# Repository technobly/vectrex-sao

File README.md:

# Vectrex SAO

Hardware and software files for the mini playable Vectrex SAO by Brett Walach.  Made for Hackaday Supercon 2022!

# Features
- Mini playable low res version of Scramble
- 7 x 10 White LED Charlieplexed display (placed in a slight perspective to match the Vectrex artwork!)
- Joystick is a 1-button capacitive touch controller
- PIC16F886 8K MCU (I had a reel of these I pulled out of the trash, which is why it uses this relatively old and huge MCU.)
- Speaker (auto mutes if not playing, or can permanently disable with removing a solder blob)
- Coily cord!  This is made of a solid core silicone wire, and stranded core silicone wire.  These were an absolute pain to make.
- Jumpers for hacking, control it via I2C directly if you want from a main badge... and there's PWM input for the speaker and touch controller output for sensing button presses available to wire to the SAO connector.
- What's a Vectrex? [https://wikipedia.org/wiki/Vectrex](https://wikipedia.org/wiki/Vectrex)
- **High score permanently saved!** Tweet a pic of your score @Technobly #vectrex-sao #supercon #badgelife

# BOM

- PCBs: 1.0mm, HASL finish, white silkscreen, black soldermask, gives a nice thin feel to them. NOTE: 1.0mm is thinner than standard PCBs!
- Don't forget to order both PCBs: 1) the main [console body](gerbers/vectrex-sao-v1.1.zip) and 2) the [controller](gerbers/vectrex-sao-controller-v1.1.zip)
- [bom/vectrex-sao-bom-both-sides.csv](bom/vectrex-sao-bom-both-sides.csv) contains all parts required to build the SAO, ready to upload to JLCPCB
- [bom/vectrex-sao-pos-both-sides.csv](bom/vectrex-sao-pos-both-sides.csv) contains the position of all parts required, ready to upload to JLCPCB
- Inner coily cord wire - 18 AWG solid core, black PVC jacket, outer diameter 1.6mm, 2.0" long with 0.25" stripped on both ends for a 1.5" long jacket. [Digikey 10982-18-1-2000-001-1-TD](https://www.digikey.com/en/products/detail/cnc-tech/10982-18-1-2000-001-1-TD/12749485)
- Outer coily cord wire - 26 AWG stranded core, black silicone jacket, outer diameter 1.3mm, ~27 turns, ~9" long. [Digikey 1175-3132-26-1-0500-001-1-TS-DS-ND](https://www.digikey.com/en/products/detail/cnc-tech/3132-26-1-0500-001-1-TS/15853654)

# Coily Cord Construction

#### 1. Wrap the 26 AWG stranded silicone wire around the 0.25" stripped end of the 18 AWG solid wire, but do not solder it yet.

#### 2. Add the controller PCB observing the proper orientation.

#### 3. Add a good amount of solder here, and push the board up against the wire bundle if possible (I did not push it up in this picture like I should have).

#### 4. Flush cut the excess wire, but leave a bit sticking out so has a little mechanical strength.

#### 5. Wrap the silicone wire 21-27 times (21 if diameter is 1.5mm, 27 if 1.3mm).  Wrap the wire tightly and keep pushing it down on the solid core as you go.  Finally twist the stranded wires around the end and while holding that tightly, clamp the wire bundle to prevent it from unwinding.

#### 6. Now add the main PCB obsererving the correct orientation.

#### 7. Add a good amount of solder here as well. Flush cut the excess wire, but leave a bit sticking out so has a little mechanical strength.

#### 8. The one on the left used 1.5mm 26 AWG wire so it has 21 wraps, and the one on the right has a slightly smaller diameter wire 1.3mm so it requires 27 wraps.  Both will work fine, but 27 wraps looks a little closer to reality :smile:

# Video of it in action:

[Youtube.com/PlayVectrex](https://youtu.be/AfYQyKARwps?si=DoC_TBigiWhMu1rB)

# License

Creative Commons Attribution-ShareAlike 4.0 International (CC BY-SA 4.0) - essentially do whatever you want, and if this is helpful to you [consider buying me a coffee](https://buymeacoffee.com/walach)  Full [LICENSE here](LICENSE)

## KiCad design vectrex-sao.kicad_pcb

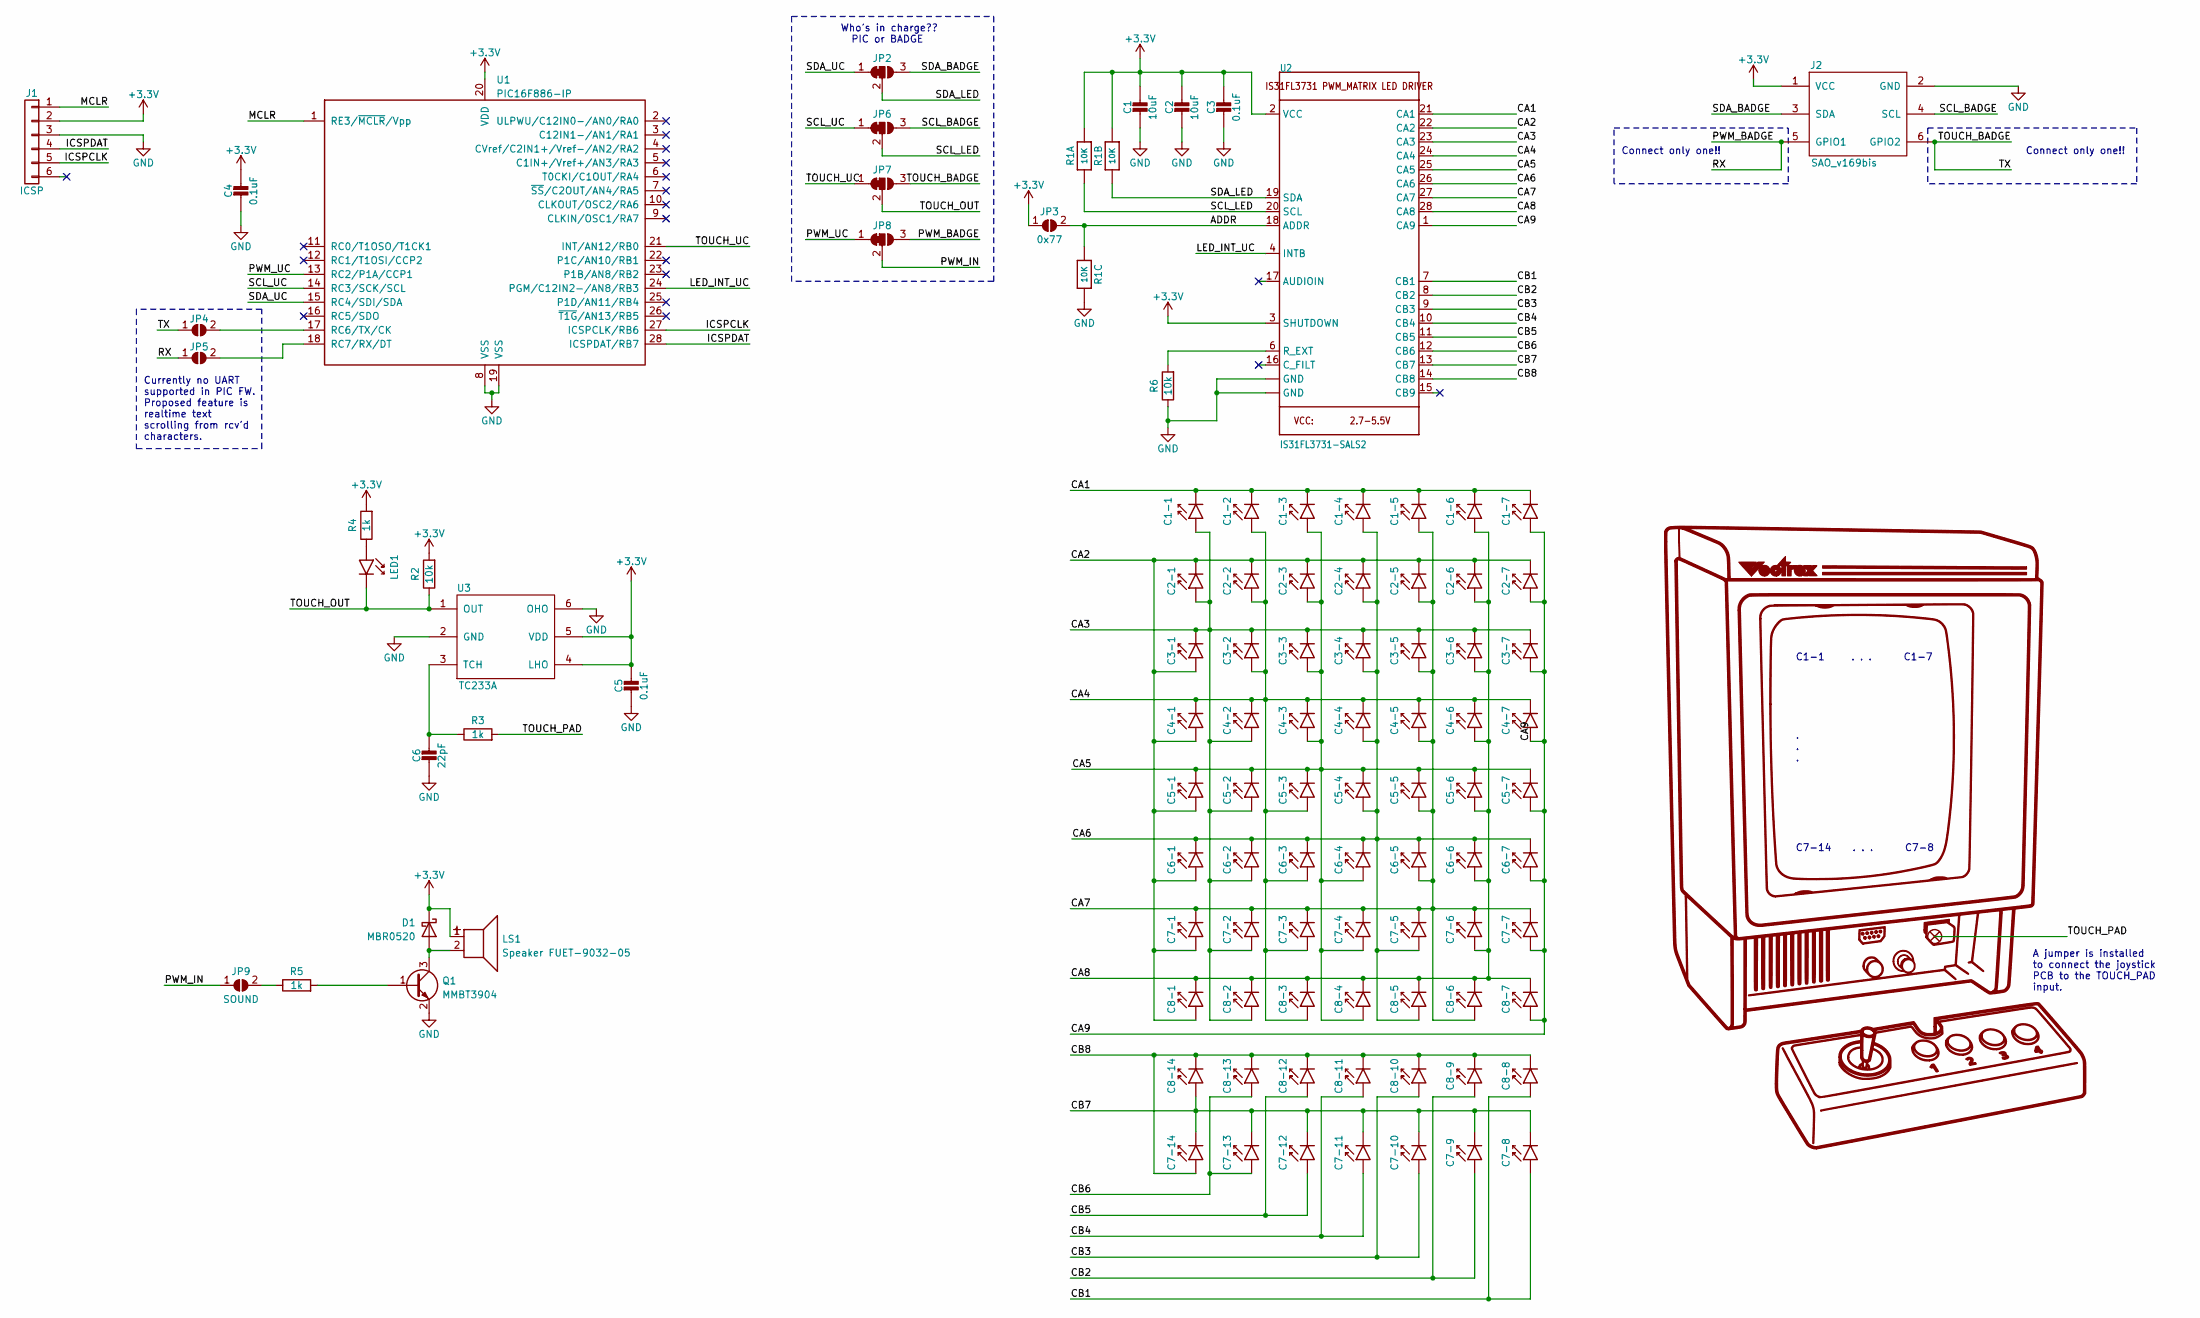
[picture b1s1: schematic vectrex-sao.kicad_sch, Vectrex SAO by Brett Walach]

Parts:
C1, C2: 10uF; C_0805_2012Metric
C1-1, C1-2, C1-3, C1-4, C1-5, C1-6, C1-7, C2-1, C2-2, C2-3, C2-4, C2-5, C2-6, C2-7, C3-1, C3-2, C3-3, C3-4, C3-5, C3-6, C3-7, C4-1, C4-2, C4-3, C4-4, C4-5, C4-6, C4-7, C5-1, C5-2, C5-3, C5-4, C5-5, C5-6, C5-7, C6-1, C6-2, C6-3, C6-4, C6-5, C6-6, C6-7, C7-1, C7-2, C7-3, C7-4, C7-5, C7-6, C7-7, C7-8, C7-9, C7-10, C7-11, C7-12, C7-13, C7-14, C8-1, C8-2, C8-3, C8-4, C8-5, C8-6, C8-7, C8-8, C8-9, C8-10, C8-11, C8-12, C8-13, C8-14: LED0603_NOOUTLINE; LED_0603_1608Metric
C3, C4: 0.1uF; C_0805_2012Metric
C5: 0.1uF; C_0603_1608Metric
C6: 22pF; C_0603_1608Metric
D1: MBR0520; D_SOD-123
J1: ICSP; PinHeader_1x06_P2.54mm_Vertical_SMD_Pin1Right
J2: SAO_v169bis; Badgelife-SAOv169-SAO-2x3
JP1: TOUCH_PAD; MountingHole_1.5mm_M2_Pad_TopOnly
JP2, JP6, JP7, JP8: solderjumper-3way; SolderJumper-3_P1.3mm_Bridged12_RoundedPad1.0x1.5mm_NumberL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
JP3: 0x77; SolderJumper-2_P1.3mm_Open_RoundedPad1.0x1.5mm
JP4: TX; SolderJumper-2_P1.3mm_Open_RoundedPad1.0x1.5mm
JP5: RX; SolderJumper-2_P1.3mm_Open_RoundedPad1.0x1.5mm
JP9: SOUND; SolderJumper-2_P1.3mm_Bridged_RoundedPad1.0x1.5mm
LED1: LED0603_NOOUTLINE; LED_0603_1608Metric
LS1: Speaker FUET-9032-05; MagneticBuzzer_FUET-9032-05
Q1: MMBT3904; SOT-23
R1: 10K; R_Array_Convex_4x0603_CAT16-F4
R2, R6: 10k; R_0603_1608Metric
R3, R4, R5: 1k; R_0603_1608Metric
U1: PIC16F886-IP; SOIC-28W_7.5x17.9mm_P1.27mm
U2: IS31FL3731-SALS2; QFN-28-1EP_4x4mm_P0.4mm_EP2.3x2.3mm
U3: TC233A; SOT-23-6

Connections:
+3.3V: C1.1, C2.1, C3.1, C4.1, C5.1, D1.1 (K), J1.2, J2.1 (VCC), JP3.1 (A), LS1.1, R1.7 (2), R1.8 (2), R2.2, R4.2, U1.20 (VDD), U2.2 (VCC), U2.3 (SHUTDOWN), U3.4 (LHO), U3.5 (VDD)
/ADDR: JP3.2 (B), R1.3 (1), U2.18 (ADDR)
/CA1: C1-1.1 (K), C1-2.1 (K), C1-3.1 (K), C1-4.1 (K), C1-5.1 (K), C1-6.1 (K), C1-7.1 (K), U2.21 (CA1)
/CA2: C2-1.1 (K), C2-2.1 (K), C2-3.1 (K), C2-4.1 (K), C2-5.1 (K), C2-6.1 (K), C2-7.1 (K), C3-1.2 (A), C4-1.2 (A), C5-1.2 (A), C6-1.2 (A), C7-1.2 (A), C8-1.2 (A), U2.22 (CA2)
/CA3: C1-1.2 (A), C2-1.2 (A), C3-1.1 (K), C3-2.1 (K), C3-3.1 (K), C3-4.1 (K), C3-5.1 (K), C3-6.1 (K), C3-7.1 (K), C4-2.2 (A), C5-2.2 (A), C6-2.2 (A), C7-2.2 (A), C8-2.2 (A), U2.23 (CA3)
/CA4: C1-2.2 (A), C2-2.2 (A), C3-2.2 (A), C4-1.1 (K), C4-2.1 (K), C4-3.1 (K), C4-4.1 (K), C4-5.1 (K), C4-6.1 (K), C4-7.1 (K), C5-3.2 (A), C6-3.2 (A), C7-3.2 (A), C8-3.2 (A), U2.24 (CA4)
/CA5: C1-3.2 (A), C2-3.2 (A), C3-3.2 (A), C4-3.2 (A), C5-1.1 (K), C5-2.1 (K), C5-3.1 (K), C5-4.1 (K), C5-5.1 (K), C5-6.1 (K), C5-7.1 (K), C6-4.2 (A), C7-4.2 (A), C8-4.2 (A), U2.25 (CA5)
/CA6: C1-4.2 (A), C2-4.2 (A), C3-4.2 (A), C4-4.2 (A), C5-4.2 (A), C6-1.1 (K), C6-2.1 (K), C6-3.1 (K), C6-4.1 (K), C6-5.1 (K), C6-6.1 (K), C6-7.1 (K), C7-5.2 (A), C8-5.2 (A), U2.26 (CA6)
/CA7: C1-5.2 (A), C2-5.2 (A), C3-5.2 (A), C4-5.2 (A), C5-5.2 (A), C6-5.2 (A), C7-1.1 (K), C7-2.1 (K), C7-3.1 (K), C7-4.1 (K), C7-5.1 (K), C7-6.1 (K), C7-7.1 (K), C8-6.2 (A), U2.27 (CA7)
/CA8: C1-6.2 (A), C2-6.2 (A), C3-6.2 (A), C4-6.2 (A), C5-6.2 (A), C6-6.2 (A), C7-6.2 (A), C8-1.1 (K), C8-2.1 (K), C8-3.1 (K), C8-4.1 (K), C8-5.1 (K), C8-6.1 (K), C8-7.1 (K), U2.28 (CA8)
/CA9: C1-7.2 (A), C2-7.2 (A), C3-7.2 (A), C4-7.2 (A), C5-7.2 (A), C6-7.2 (A), C7-7.2 (A), C8-7.2 (A), U2.1 (CA9)
/CB1: C7-8.2 (A), C8-8.2 (A), U2.7 (CB1)
/CB2: C7-9.2 (A), C8-9.2 (A), U2.8 (CB2)
/CB3: C7-10.2 (A), C8-10.2 (A), U2.9 (CB3)
/CB4: C7-11.2 (A), C8-11.2 (A), U2.10 (CB4)
/CB5: C7-12.2 (A), C8-12.2 (A), U2.11 (CB5)
/CB6: C7-13.2 (A), C8-13.2 (A), U2.12 (CB6)
/CB7: C7-8.1 (K), C7-9.1 (K), C7-10.1 (K), C7-11.1 (K), C7-12.1 (K), C7-13.1 (K), C7-14.1 (K), C8-14.2 (A), U2.13 (CB7)
/CB8: C7-14.2 (A), C8-8.1 (K), C8-9.1 (K), C8-10.1 (K), C8-11.1 (K), C8-12.1 (K), C8-13.1 (K), C8-14.1 (K), U2.14 (CB8)
/ICSPCLK: J1.5, U1.27 (ICSPCLK/RB6)
/ICSPDAT: J1.4, U1.28 (ICSPDAT/RB7)
/LED_INT_UC: U1.24 (PGM/C12IN2-/AN8/RB3), U2.4 (INTB)
/MCLR: J1.1, U1.1 (RE3/~MCLR/Vpp)
/PWM_BADGE: J2.5 (GPIO1), JP5.1 (A), JP8.3 (B)
/PWM_IN: JP8.2 (C), JP9.1 (A)
/PWM_UC: JP8.1 (A), U1.13 (RC2/P1A/CCP1)
/SCL_BADGE: J2.4 (SCL), JP6.3 (B)
/SCL_LED: JP6.2 (C), R1.1, U2.20 (SCL)
/SCL_UC: JP6.1 (A), U1.14 (RC3/SCK/SCL)
/SDA_BADGE: J2.3 (SDA), JP2.3 (B)
/SDA_LED: JP2.2 (C), R1.2 (1), U2.19 (SDA)
/SDA_UC: JP2.1 (A), U1.15 (RC4/SDI/SDA)
/TOUCH_BADGE: J2.6 (GPIO2), JP4.1 (A), JP7.3 (B)
/TOUCH_OUT: JP7.2 (C), LED1.1 (K), R2.1, U3.1 (OUT)
/TOUCH_PAD: JP1.1 (TP), R3.2
/TOUCH_UC: JP7.1 (A), U1.21 (INT/AN12/RB0)
GND: C1.2, C2.2, C3.2, C4.2, C5.2, C6.2, J1.3, J2.2 (GND), Q1.2 (E), R1.6 (2), R6.1, U1.8 (VSS), U1.19 (VSS), U2.5 (GND), U2.29 (GND), U3.2 (GND), U3.6 (OHO)
unnamed: D1.2 (A), LS1.2, Q1.3 (C)
unnamed: JP4.2 (B), U1.17 (RC6/TX/CK)
unnamed: JP5.2 (B), U1.18 (RC7/RX/DT)
unnamed: JP9.2 (B), R5.1
unnamed: LED1.2 (A), R4.1
unnamed: Q1.1 (B), R5.2
unnamed: R6.2, U2.6 (R_EXT)
unnamed: C6.1, R3.1, U3.3 (TCH)

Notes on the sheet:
Who's in charge?? PIC or BADGE
A jumper is installed to connect the joystick PCB to the TOUCH_PAD input.
Connect only one!!
Currently no UART supported in PIC FW. Proposed feature is realtime text scrolling from rcv'd characters.
C1-1 . . . C1-7 . . . C7-14 . . . C7-8

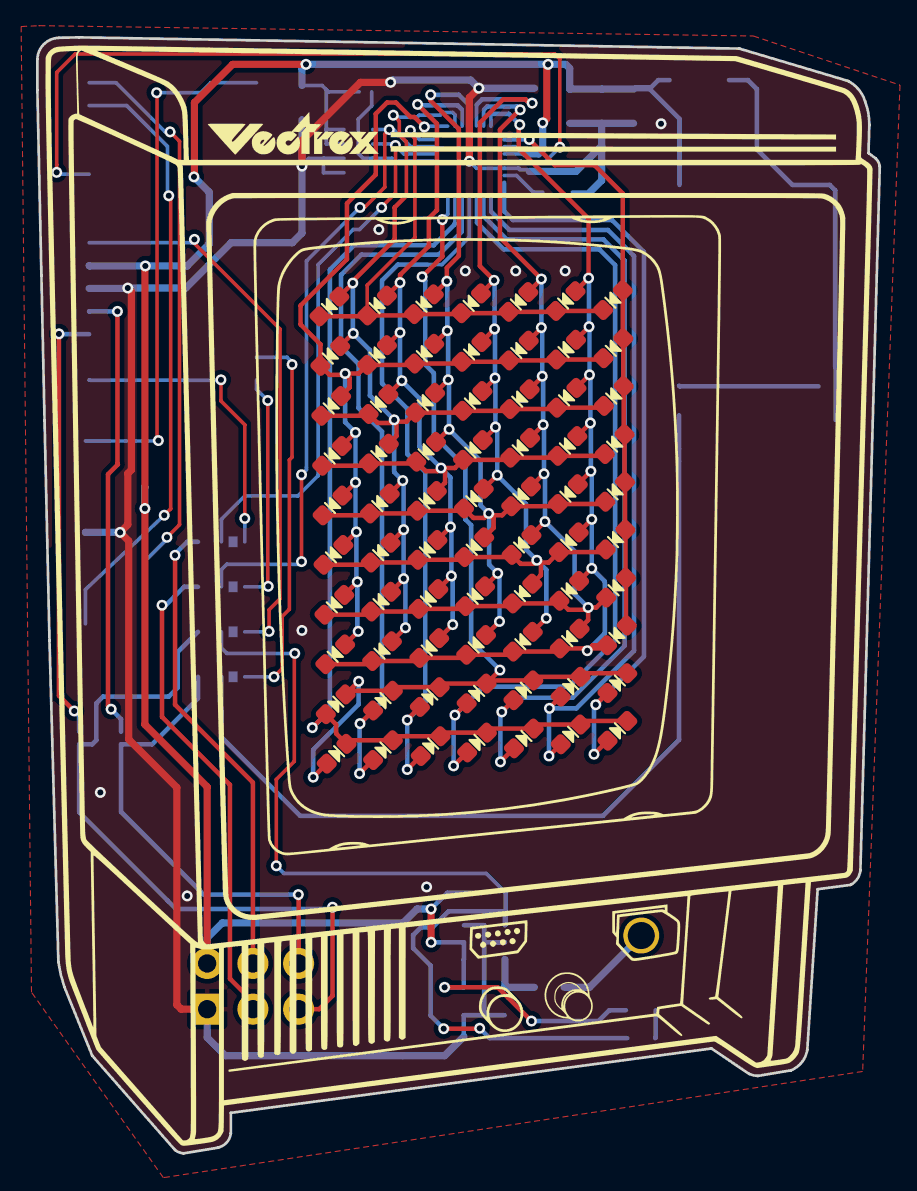
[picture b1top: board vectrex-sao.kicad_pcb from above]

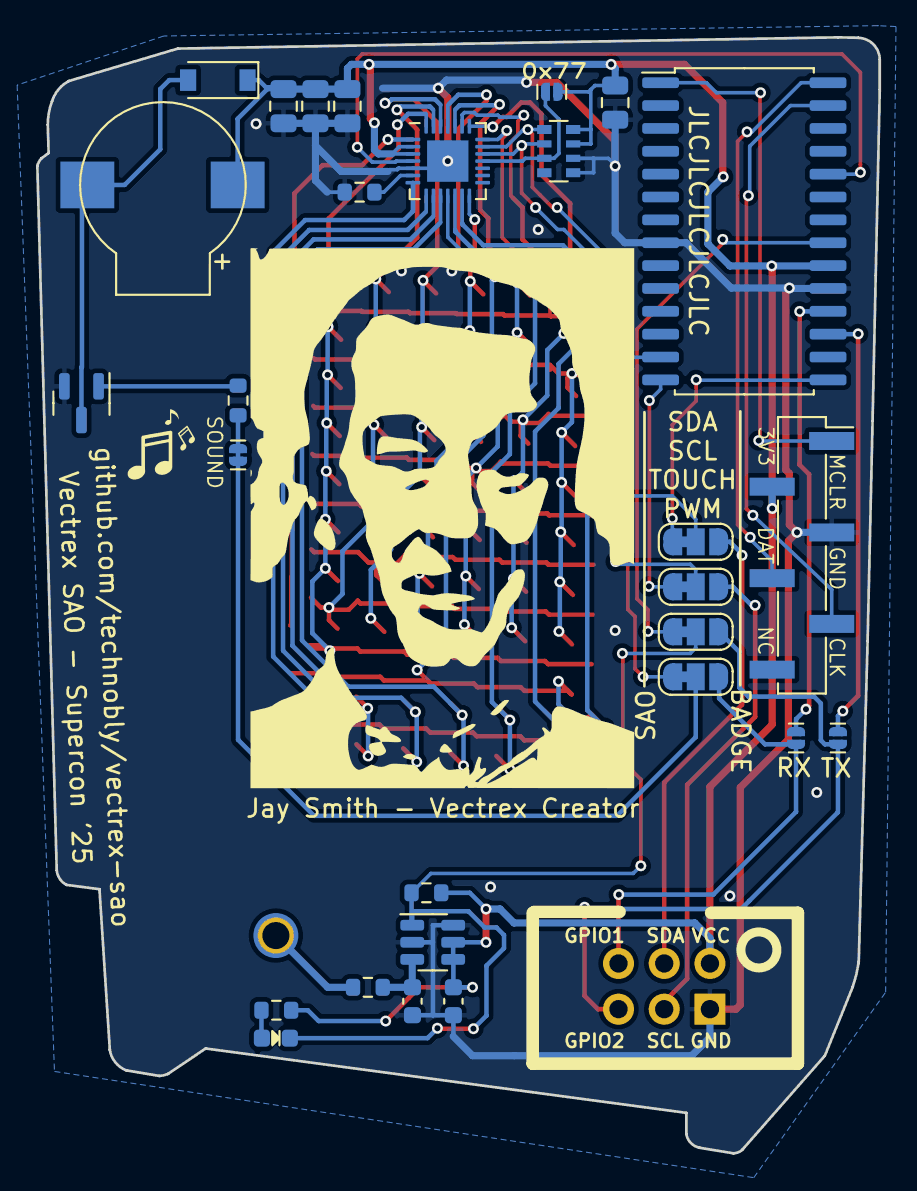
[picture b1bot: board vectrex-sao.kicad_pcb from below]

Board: 2 copper layers, 46.8 x 62.0 mm, 100 parts (29 on the bottom side), 45 nets.

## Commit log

2022-09-25 4 hours of work redone in 1 hour
2022-09-25 tweaks
2022-09-25 rearrange the bottom two rows
2022-09-28 rearranged parts, add temp silk, grid 2.54mm
2022-10-01 finished outline, added controller board
2022-10-26 updated models and created files for ordering
2022-10-26 added code
2022-11-03 added final features and cleanup
2022-11-03 add README.md and LICENSE
2022-11-04 added note about high score save
2024-11-14 minor update to mplab project files
2024-11-14 update 3D models
2024-11-15 update BOM and add coily cord construction pics
2024-11-15 add wire to BOM
2024-11-16 minor updates to README
2024-11-21 update BOM references to remove trailing ', ' and make LS2 DNP
2025-01-17 update files for easier mass production with JLCPCB
